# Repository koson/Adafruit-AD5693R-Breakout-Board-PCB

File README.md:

## Adafruit AD5693R Breakout Board - 16-Bit DAC with I2C Interface - STEMMA QT / qwiic PCB

<a href="http://www.adafruit.com/products/5811"><br/>
Click here to purchase one from the Adafruit shop</a>

PCB files for the Adafruit AD5693R Breakout Board - 16-Bit DAC with I2C Interface - STEMMA QT / qwiic. 

Format is EagleCAD schematic and board layout
* https://www.adafruit.com/product/5811

### Description

Which is better, less bits or more? MORE of course! So why settle for a 12-bit DAC like the MCP4725 when you can go for the 16-bits of the AD5693? OK well there may be some reason to go with 12-bits, say if you don't need high resolution output and want to go with the more affordable DAC. But for those who like the finer things in life, the Adafruit AD5693R Breakout Board is a16-Bit DAC with I2C Interface and temperature compensated 2.5V internal reference  for a compact high-precision output. 

We break out the ADDR/A0 pin so you can connect two of these DACs on one I2C bus, just tie the A0 pin high (or close the jumper on the back) to keep it from conflicting. Also included is a 6-pin header, for use in a breadboard. Works with both 3.3V or 5V logic, and you can have the output max out at 2.5V or 5V (2xVref). If you're powering from 3.3V you will be able to set the output range to 2.5V or Vin.

Some nice extras with this chip: for chips that have 3.4Mbps Fast Mode I2C (Arduino's don't) you can update the Vout at ~200 KHz. There's an EEPROM so if you write the output voltage, you can 'store it' so if the device is power cycled it will restore that voltage. The output voltage is rail-to-rail and proportional to the power pin so if you run it from 3.3V, the output range is 0-3.3V. If you run it from 5V the output range is 0-5V.

We have an easy-to-use Arduino library and tutorial with a sine-wave output example that can be used with just about any microcontroller or microcomputer with I2C host.

Comes with a bit of 0.1" standard header in case you want to use it with a breadboard or perfboard.  Four mounting holes for easy attachment. There's an optional 3.5mm terminal block spot on the PCB - we don't include a 3.5mm terminal block but they're both common and stocked in the shop - that you can solder in place if you like.

To get you going fast, we spun up a custom-made PCB in the STEMMA QT form factor, making it easy to interface with. The STEMMA QT connectors on either side are compatible with the SparkFun Qwiic I2C connectors. This allows you to make solderless connections between your development board and the AD5693R or to chain it with a wide range of other sensors and accessories using a compatible cable.

QT Cable is not included, but we have a variety in the shop. 

### License

Adafruit invests time and resources providing this open source design, please support Adafruit and open-source hardware by purchasing products from [Adafruit](https://www.adafruit.com)!

Designed by Limor Fried/Ladyada for Adafruit Industries.

Creative Commons Attribution/Share-Alike, all text above must be included in any redistribution. 
See license.txt for additional details.

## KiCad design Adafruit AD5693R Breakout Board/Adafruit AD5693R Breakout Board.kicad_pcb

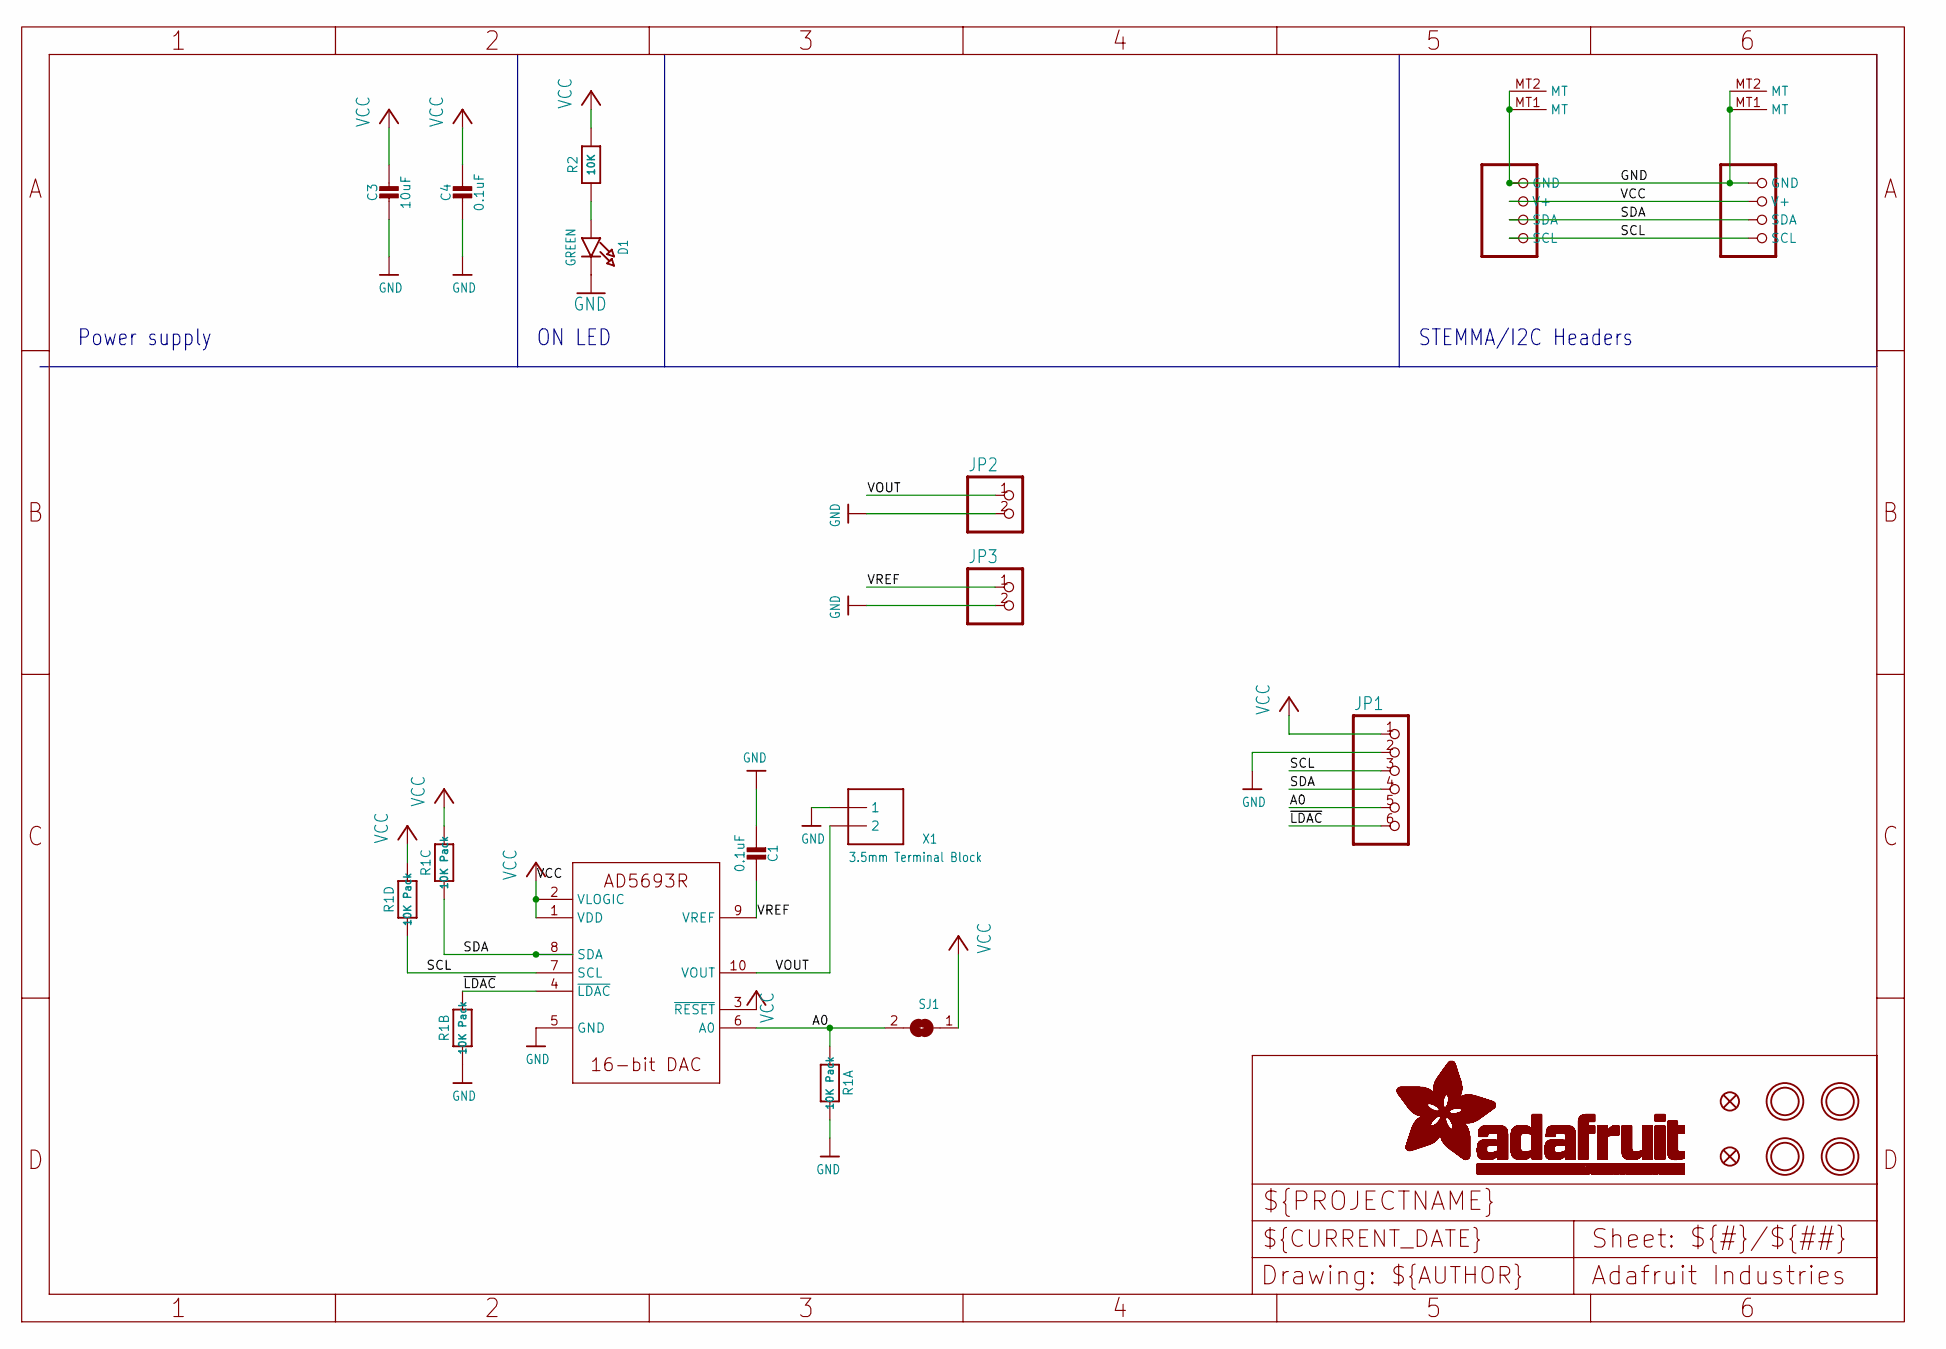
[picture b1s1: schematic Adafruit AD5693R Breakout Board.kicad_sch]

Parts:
C1, C4: 0.1uF; 0603-NO
C3: 10uF; 0805-NO
CONN3, CONN4: STEMMA_I2C_QT; JST_SH4
D1: GREEN; CHIPLED_0603_NOOUTLINE
FID3, FID4: FIDUCIAL_1MM
IC2: AD5693R_10PIN_RMZ; MSOP10
JP1: HEADER-1X670MIL; 1X06_ROUND_70
JP2, JP3: HEADER-1X2ROUND; 1X02_ROUND
R1: 10K Pack; RESPACK_4X0603
R2: 10K; 0603-NO
SJ1: SOLDERJUMPER; SOLDERJUMPER_ARROW_NOPASTE
U$20, U$21, U$25, U$27: MOUNTINGHOLE2.5; MOUNTINGHOLE_2.5_PLATED
X1: 3.5mm Terminal Block; TERMBLOCK_1X2-3.5MM

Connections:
A0: IC2.6 (A0), JP1.5, R1.8 (2), SJ1.2
GND: C1.2, C3.2, C4.2, CONN3.1 (GND), CONN3.MT1 (MT), CONN3.MT2 (MT), CONN4.1 (GND), CONN4.MT1 (MT), CONN4.MT2 (MT), D1.C, IC2.5 (GND), JP1.2, JP2.2, JP3.2, R1.1, R1.2 (1), X1.1
unnamed: D1.A, R2.1
SCL: CONN3.4 (SCL), CONN4.4 (SCL), IC2.7 (SCL), JP1.3, R1.4 (1)
SDA: CONN3.3 (SDA), CONN4.3 (SDA), IC2.8 (SDA), JP1.4, R1.3 (1)
VCC: C3.1, C4.1, CONN3.2 (V+), CONN4.2 (V+), IC2.1 (VDD), IC2.2 (VLOGIC), IC2.3 (~RESET), JP1.1, R1.5 (2), R1.6 (2), R2.2, SJ1.1
VOUT: IC2.10 (VOUT), JP2.1, X1.2
VREF: C1.1, IC2.9 (VREF), JP3.1
~LDAC: IC2.4 (~LDAC), JP1.6, R1.7 (2)

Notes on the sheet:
STEMMA/I2C Headers
Power supply
ON LED

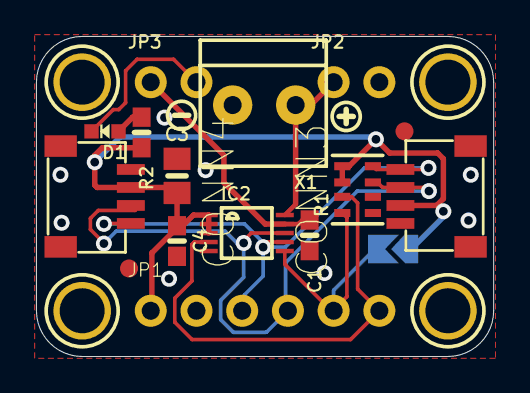
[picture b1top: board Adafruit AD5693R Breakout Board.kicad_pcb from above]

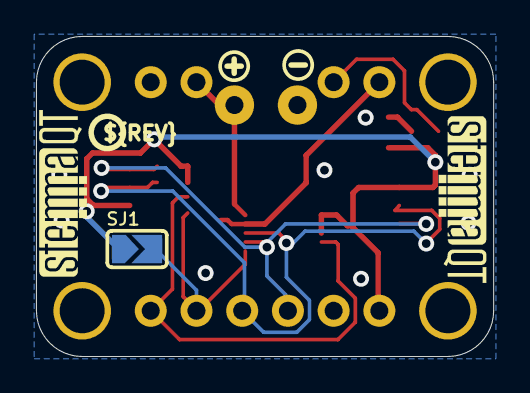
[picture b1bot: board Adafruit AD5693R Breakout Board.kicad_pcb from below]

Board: 2 copper layers, 25.4 x 17.8 mm, 43 parts (11 on the bottom side), 9 nets.

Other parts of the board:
PLABEL0: PLABEL0
PLABEL1: PLABEL1
PLABEL2: PLABEL2
PLABEL3: PLABEL3
PLABEL4: PLABEL4
PLABEL5: PLABEL5
PLABEL6: PLABEL6
PLABEL7: PLABEL7
PLABEL8: PLABEL8
PLABEL9: PLABEL9
PLABEL10: PLABEL10
PLABEL11: PLABEL11
PLABEL12: PLABEL12
PLABEL13: PLABEL13
PLABEL14: PLABEL14
PLABEL15: PLABEL15
U$2, U$7: SYMBOL_PLUS
U$4, U$5: SYMBOL_MINUS
U$8: PCBFEAT-REV-040
U$31, U$32: STEMMAQT

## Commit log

2023-09-27 adding cookiecutter output
2024-03-18 Import to Kicad
2024-04-01 add kicad project
